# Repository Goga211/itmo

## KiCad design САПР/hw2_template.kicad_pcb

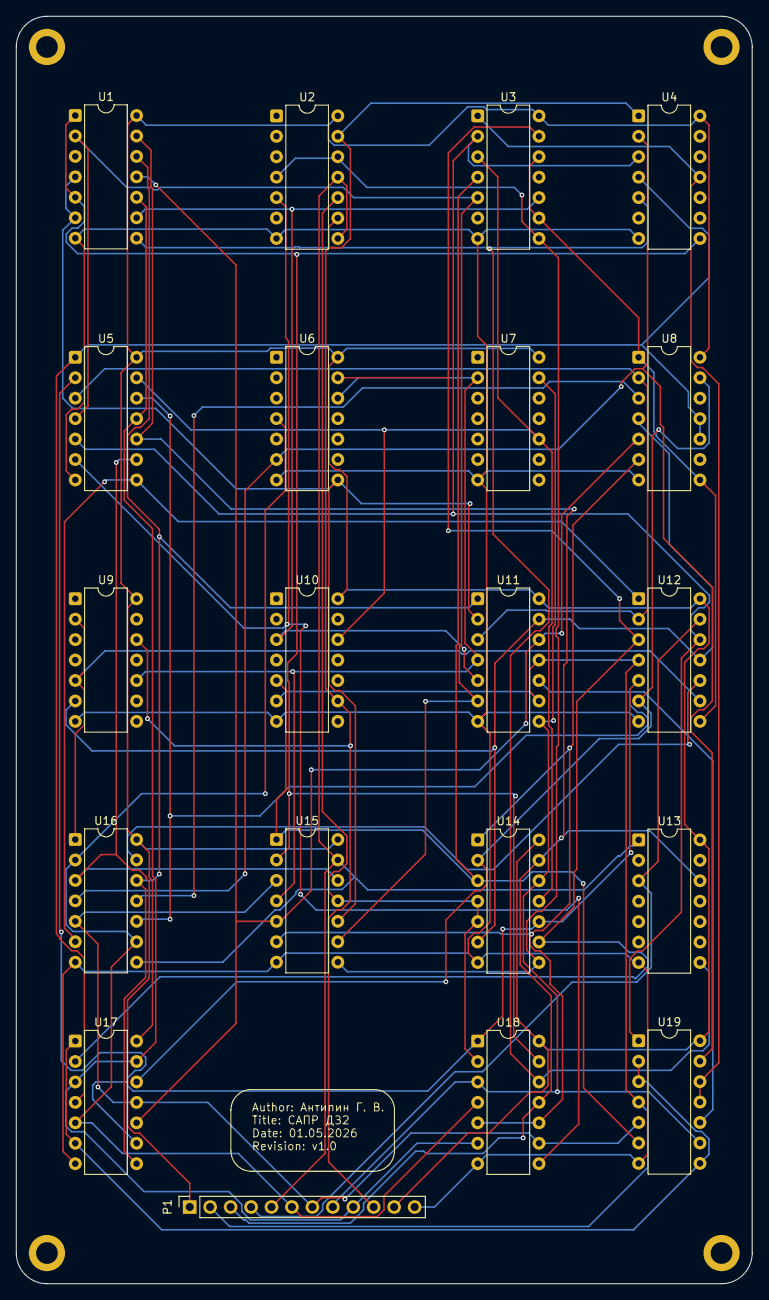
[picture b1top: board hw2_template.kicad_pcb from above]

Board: 2 copper layers, 91.4 x 157.5 mm, 24 parts (0 on the bottom side), 42 nets.

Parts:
P1: Conn_01x12; PinSocket_1x12_P2.54mm_Vertical
REF01, REF02, REF03, REF04: 2.7mm_M2.5_ISO7380_Pad; MountingHole_2.7mm_M2.5_ISO7380_Pad
U1, U2, U3, U4, U5, U6, U7, U8, U9, U10, U11, U12, U13, U14, U15, U16, U17, U18, U19: DS8830; DIP-14_W7.62mm

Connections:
GND: P1.12, U1.7, U2.7, U3.7, U4.7, U5.7, U6.7, U7.7, U8.7, U9.7, U10.7, U11.7, U12.7, U13.7, U14.7, U15.7, U16.7, U17.7, U18.7, U19.7
VCC: P1.11, U1.14, U2.14, U3.14, U4.14, U5.14, U6.14, U7.14, U8.14, U9.14, U10.14, U11.14, U12.14, U13.14, U14.14, U15.14, U16.14, U17.14, U18.14, U19.14
net1: U3.2, U4.3, U5.5, U12.12, U19.1
net2: P1.7, U15.3, U16.5, U17.11, U18.9, U19.5
net3: U3.1, U4.11, U19.11, U19.12
net4: U5.3, U8.2, U11.3, U12.2
net5: U8.3, U16.11
net6: U3.13, U6.13, U12.3, U14.9, U17.2
net7: U17.1, U17.6, U19.2, U19.3, U19.8
net8: U5.12, U11.10, U16.10, U19.10
net9: U3.4, U10.5, U14.3, U15.1, U19.6
net10: P1.2, U10.6, U11.9, U11.11, U12.4, U19.4
net11: U5.2, U12.5, U14.10, U17.9, U18.1
net12: U4.2, U6.6, U16.4, U19.13
net13: P1.8, U7.13, U11.8, U14.12, U18.3, U19.9
net14: U1.9, U3.10, U10.3, U11.5
net15: U1.8, U4.5, U13.8, U18.12
net16: U2.10, U14.4, U14.5, U15.11, U18.2
net17: P1.9, U1.10, U5.11, U17.3, U17.13, U18.6
net18: U12.10, U16.13
net19: U8.6, U14.1, U15.6, U18.5, U18.10
net20: U3.9, U3.12, U8.1, U8.8, U12.8
net21: P1.4, U12.13, U13.3
net22: U8.4, U9.6, U11.13, U12.11, U14.6
net23: P1.3, U1.13, U5.10, U13.12, U14.13, U18.11
net24: U8.13, U12.6, U14.2, U17.12
net25: U1.12, U11.1, U16.12, U17.8
net26: P1.6, U6.4, U16.2, U16.9, U17.5, U18.4
net27: U1.4, U1.6, U6.8, U11.2, U15.10
net28: U2.4, U2.12, U3.8, U14.8, U15.8
net29: U3.3, U5.13, U7.10, U10.12, U14.11
net30: P1.1, U5.9, U15.12, U16.3
net31: U2.5, U5.6, U18.8
net32: U1.1, U1.5, U4.8, U15.2, U18.13
net33: U1.2, U3.5, U5.4, U11.6, U15.9
net34: U5.8, U12.1, U16.6
net35: P1.5, U2.8, U2.11, U13.1, U15.13, U16.8
net36: U1.11, U8.5, U11.12, U15.5, U17.10
net37: U4.4, U5.1, U8.10, U8.11, U17.4
net38: U9.2, U9.5, U12.9, U16.1
net39: U6.12, U7.2, U9.10, U11.4, U15.4
net40: P1.10, U2.9, U2.13, U4.1, U9.12, U10.9

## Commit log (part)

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2026-02-06 5 sem done
